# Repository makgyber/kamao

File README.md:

# Kamao Wireless Split Keyboard

## Features
- uses Seeeduino XIAO BLE 
- split wireless via bluetooth
- 32 keys
- low-profile using choc v1 
- reversible pcb

## Why did I build this?

This was an experiment of sorts for me. I had found that I really liked the Sweep, but wanted a wireless version.
I also wanted to see if I could assemble the board in such a way that the MCU's were both right-side up using software 
to make it work (I couldn"t find a reversible footprint for the Xiao BLE).

## Building

Kicad files are in the kamao folder; I also provided the gerber files so you can just zip them up and upload to your
preferred pcb manufacturer.

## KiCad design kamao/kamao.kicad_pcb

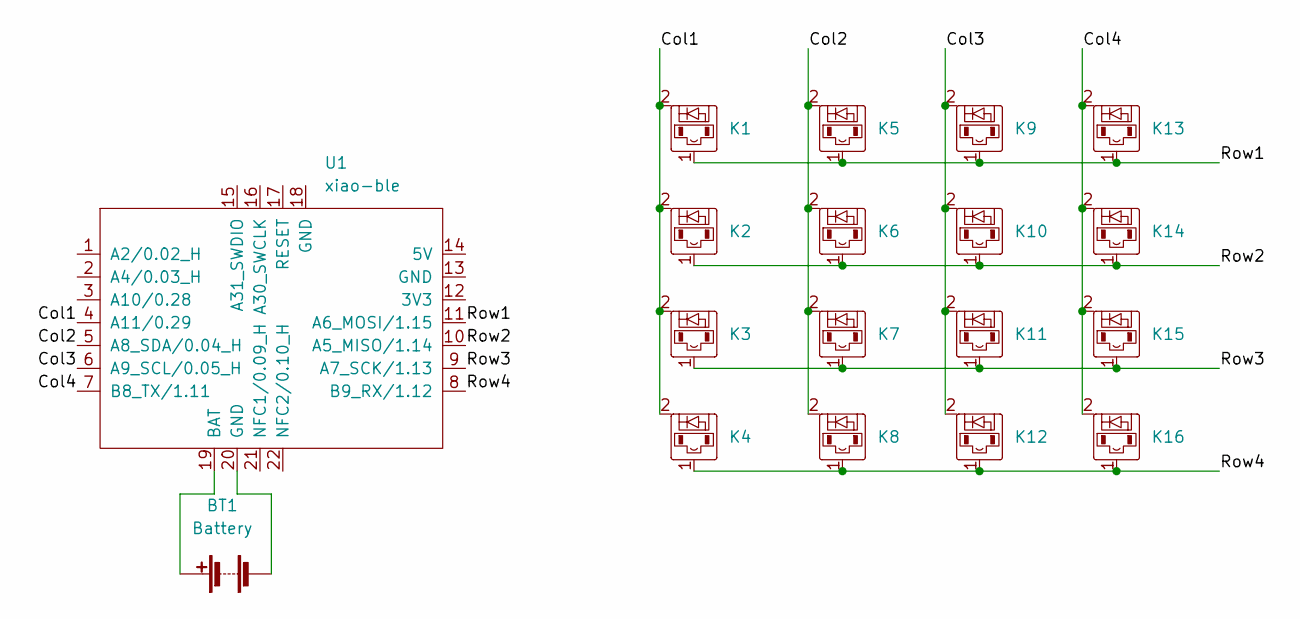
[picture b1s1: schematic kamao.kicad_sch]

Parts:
BT1: Battery; JST_EH_B2B-EH-A_1x02_P2.50mm_Vertical
K1, K2, K3, K4, K5, K6, K7, K8, K9, K10, K11, K12, K13, K14, K15, K16: diode-choc; pg1350-DR
U1: xiao-ble; xiao-ble-tht

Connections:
/Col1: K1.2, K2.2, K3.2, K4.2, U1.4 (A11/0.29)
/Col2: K5.2, K6.2, K7.2, K8.2, U1.5 (A8_SDA/0.04_H)
/Col3: K9.2, K10.2, K11.2, K12.2, U1.6 (A9_SCL/0.05_H)
/Col4: K13.2, K14.2, K15.2, K16.2, U1.7 (B8_TX/1.11)
/Row1: K1.1, K5.1, K9.1, K13.1, U1.11 (A6_MOSI/1.15)
/Row2: K2.1, K6.1, K10.1, K14.1, U1.10 (A5_MISO/1.14)
/Row3: K3.1, K7.1, K11.1, K15.1, U1.9 (A7_SCK/1.13)
/Row4: K4.1, K8.1, K12.1, K16.1, U1.8 (B9_RX/1.12)
unnamed: BT1.1 (+), U1.19 (BAT)
unnamed: BT1.2 (-), U1.20 (GND)

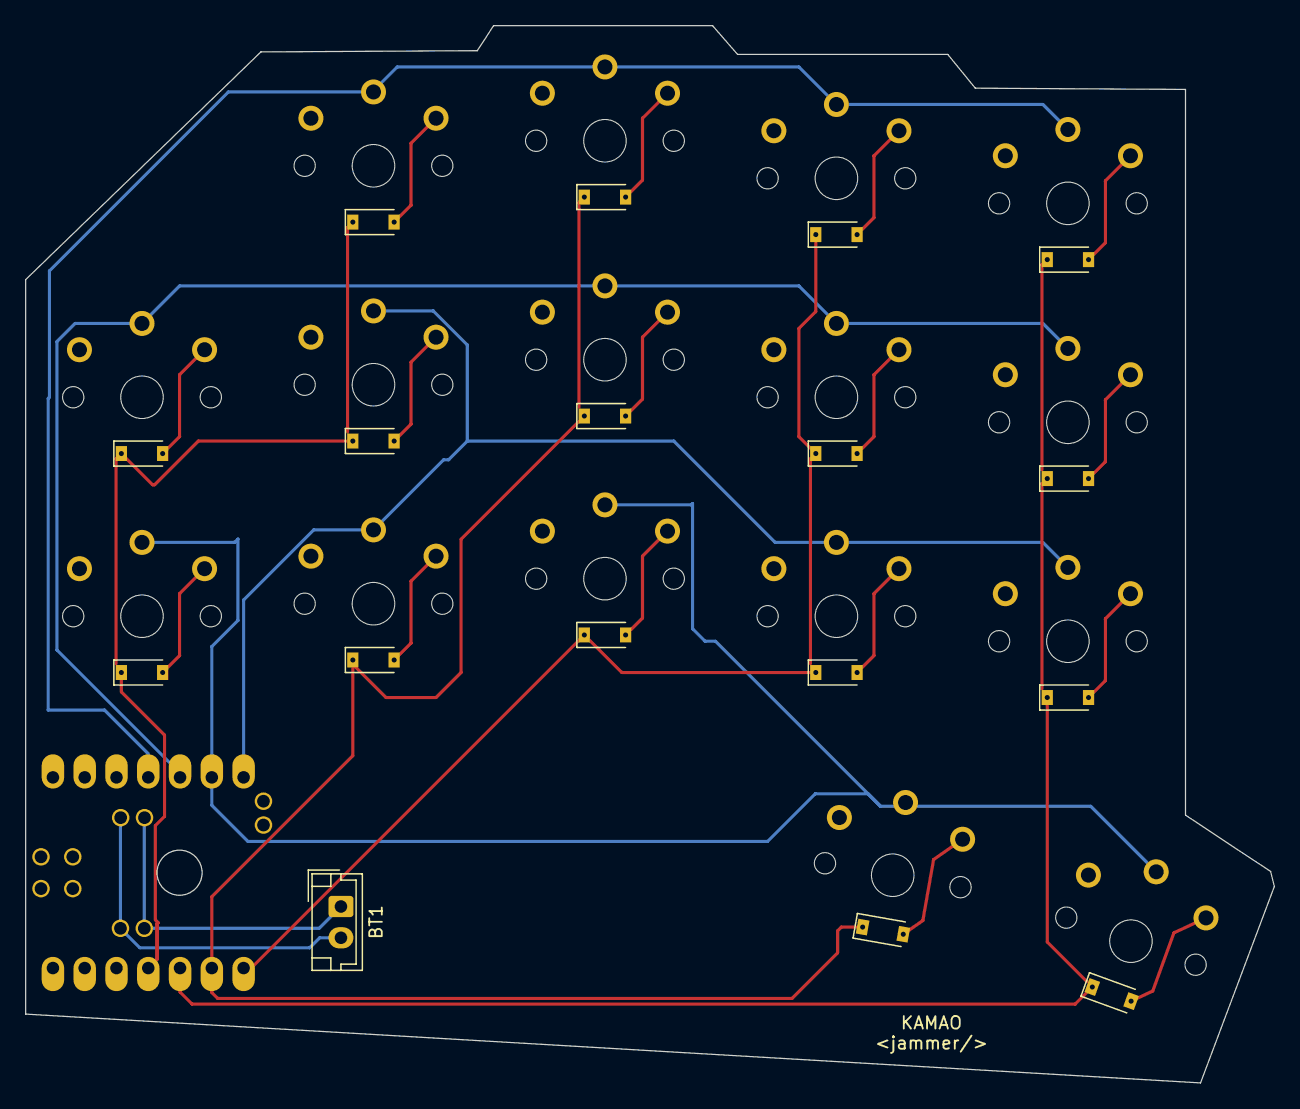
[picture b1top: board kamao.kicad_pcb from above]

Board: 2 copper layers, 99.8 x 84.5 mm, 18 parts (0 on the bottom side), 10 nets.

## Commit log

2022-10-26 working board
2022-10-26 fix structure and keymap
2022-10-31 revise keymzp
2022-11-01 for publishing
